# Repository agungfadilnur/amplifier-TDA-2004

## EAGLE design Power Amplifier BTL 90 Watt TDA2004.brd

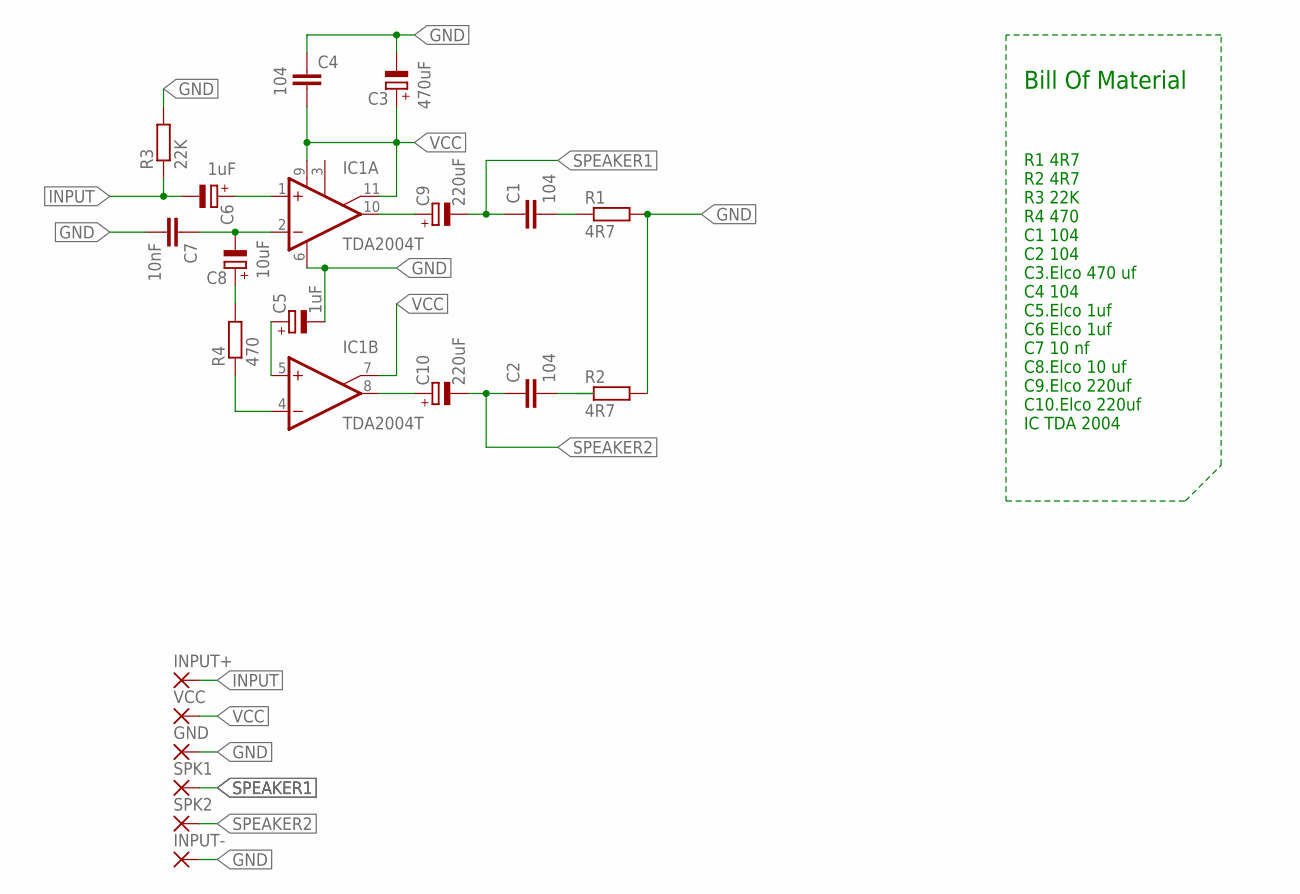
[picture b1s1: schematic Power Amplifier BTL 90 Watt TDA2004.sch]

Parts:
C1, C2, C4: 104; C025-025X050
C3: 470uF; E1,8-4
C5, C6: 1uF; E1,8-4
C7: 10nF; C025-025X050
C8: 10uF; E1,8-4
C9, C10: 220uF; E1,8-4
GND: 1,6/0,8
IC1: TDA2004T; SIP11
INPUT+: 1,6/0,8
INPUT-: 1,6/0,8
R1, R2: 4R7; 0204/7
R3: 22K; 0204/7
R4: 470; 0204/7
SPK1, SPK2: 1,6/0,8
VCC: 1,6/0,8

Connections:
GND: C3.-, C4.1, C5.-, C7.2, GND.1, IC1.6 (GND), INPUT-.1, R1.2, R2.2, R3.2
INPUT: C6.-, INPUT+.1, R3.1
unnamed: C9.+, IC1.10 (OUT)
unnamed: C1.2, R1.1
unnamed: C10.+, IC1.8 (OUT)
unnamed: C2.2, R2.1
unnamed: C6.+, IC1.1 (+IN)
unnamed: C7.1, C8.-, IC1.2 (-IN)
unnamed: C8.+, R4.2
unnamed: IC1.4 (-IN), R4.1
unnamed: C5.+, IC1.5 (+IN)
SPEAKER1: C1.1, C9.-, SPK1.1
SPEAKER2: C2.1, C10.-, SPK2.1
VCC: C3.+, C4.2, IC1.7 (BTSP), IC1.9 (V+), IC1.11 (BTSP), VCC.1

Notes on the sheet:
R1 4R7 R2 4R7 R3 22K R4 470 C1 104 C2 104 C3.Elco 470 uf C4 104 C5.Elco 1uf C6 Elco 1uf C7 10 nf C8.Elco 10 uf C9.Elco 220uf C10.Elco 220uf IC TDA 2004
Bill Of Material

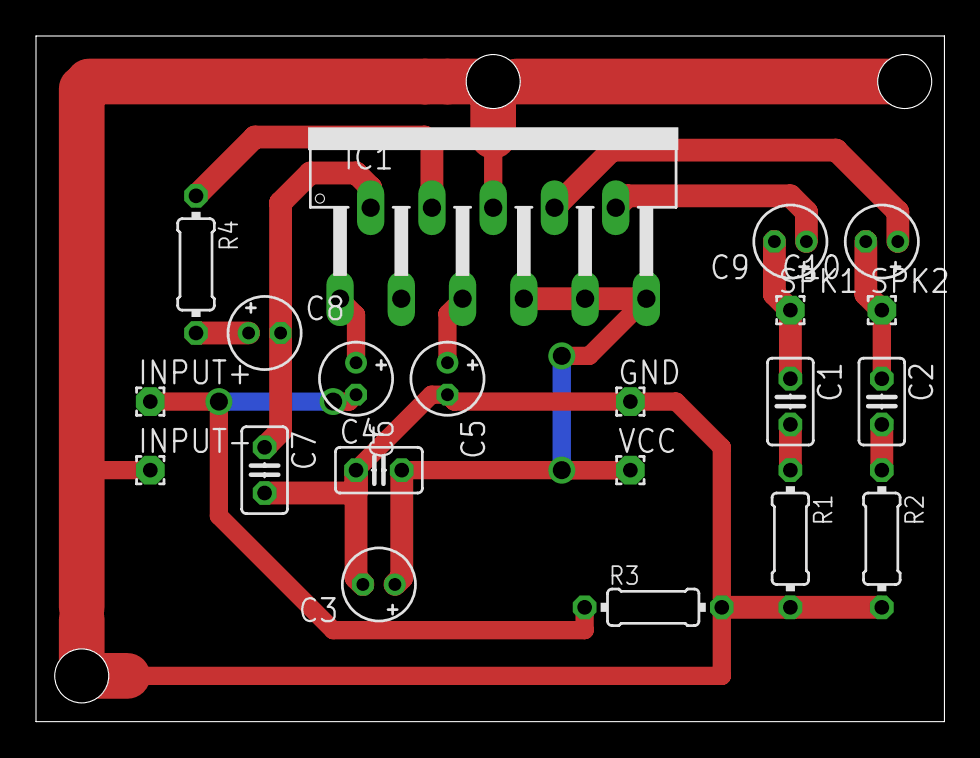
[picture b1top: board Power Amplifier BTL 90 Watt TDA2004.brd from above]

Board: 2 copper layers, 50.5 x 38.1 mm, 21 parts (0 on the bottom side), 14 nets.

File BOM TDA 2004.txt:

R1 4R7
R2 4R7
R3 22K
R4 470
C1 104
C2 104
C3.Elco 470 uf
C4 104
C5 1uf
C6 1uf
C7 10 nf
C8.Elco 10 uf 
C9.Elco 220uf
C10.Elco 220uf
IC TDA 2004
